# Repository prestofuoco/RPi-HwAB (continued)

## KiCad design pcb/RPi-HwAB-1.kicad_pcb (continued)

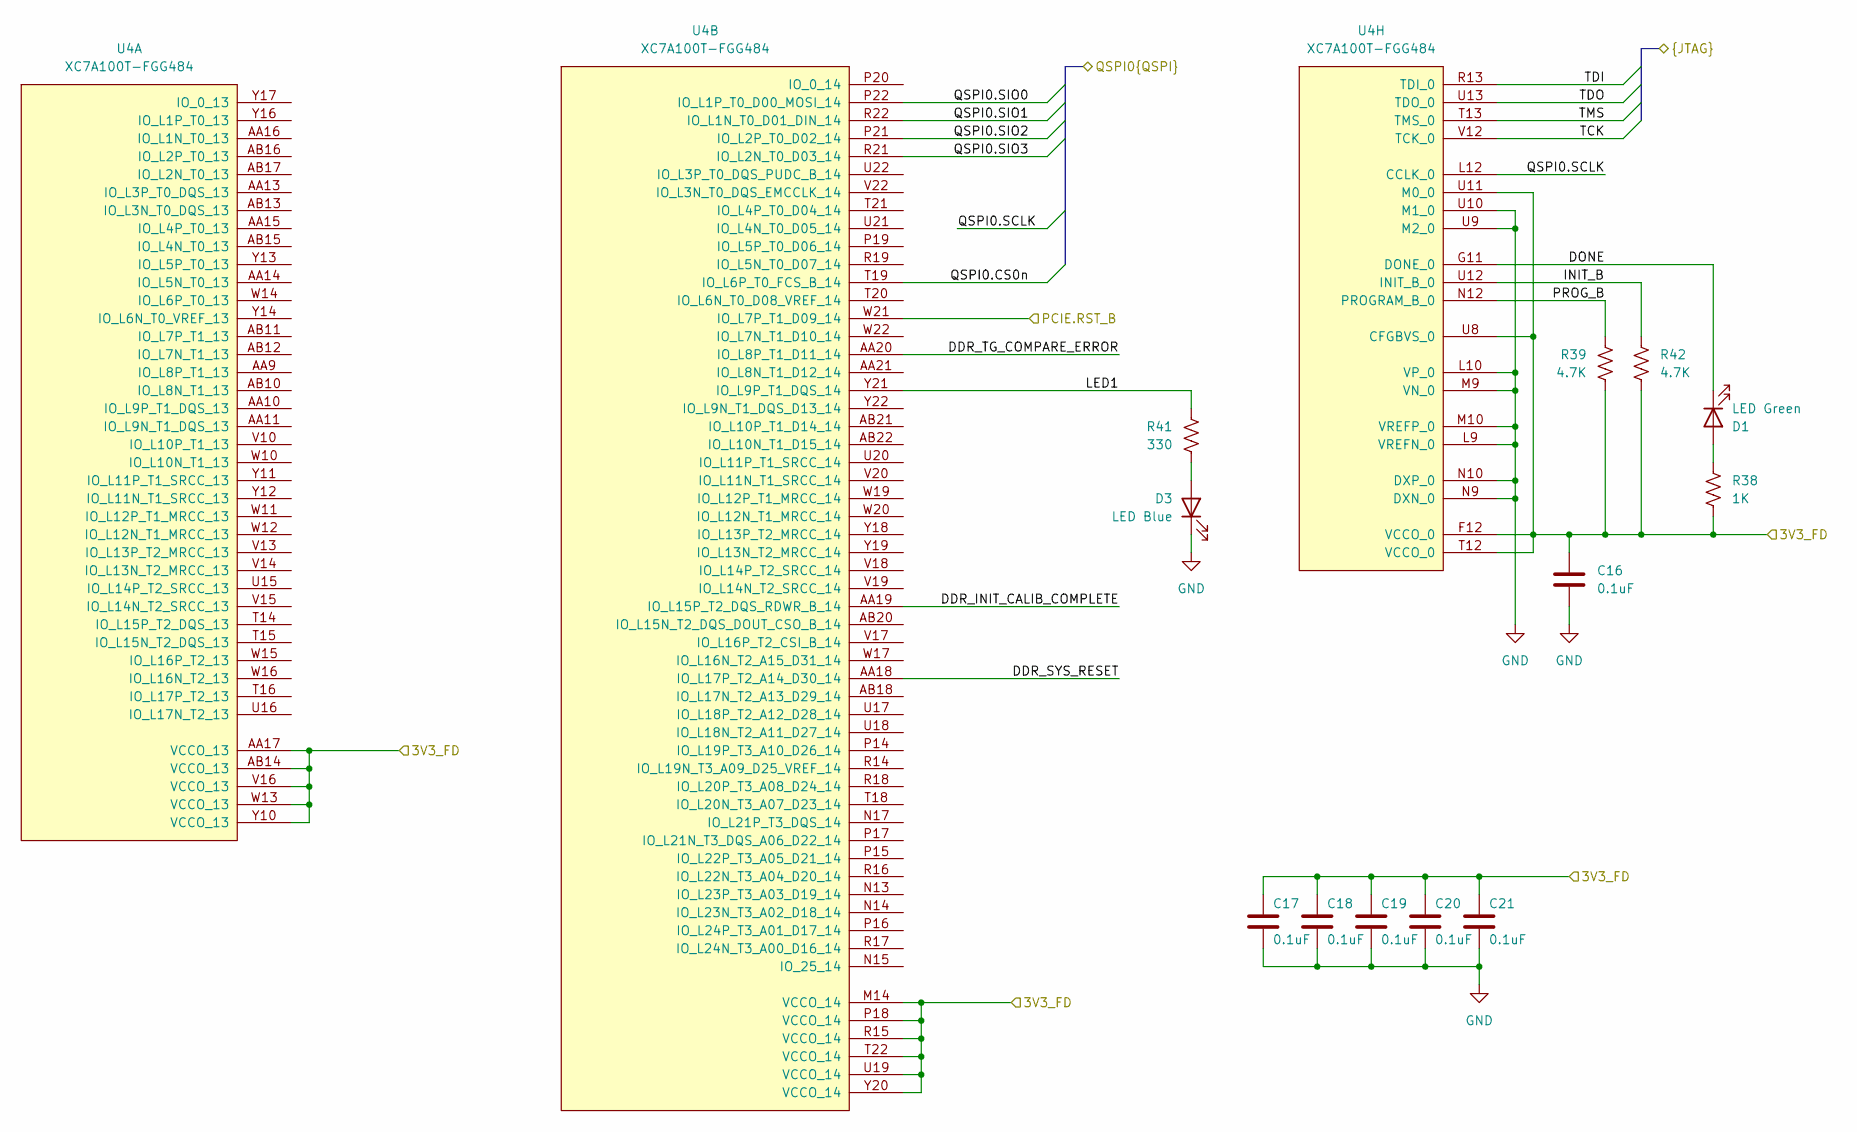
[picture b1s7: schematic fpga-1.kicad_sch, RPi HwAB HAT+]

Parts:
C16, C17, C18, C19, C20, C21: 0.1uF; C_0402_1005Metric; Part Description CAP CER 0.1UF 16V X7R 0402
D1: LED Green; LED_0603_1608Metric; Part Description LED GREEN CLEAR CHIP SMD
D3: LED Blue; LED_0603_1608Metric; Part Description LED BLUE CLEAR CHIP SMD
R38: 1K; R_0402_1005Metric; Part Description RES 1K OHM 5% 1/16W 0402
R39, R42: 4.7K; R_0402_1005Metric; Part Description RES 4.7K OHM 1% 1/16W 0402
R41: 330; R_0402_1005Metric; Part Description RES 330 OHM 1% 1/16W 0402
U4: XC7A100T-FGG484; Xilinx_FGG484; Part Description IC FPGA 285 I/O 484FBGA

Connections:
/Connectors/3V3_FD: C16.2, C17.2, C18.2, C19.2, C20.2, C21.2, R38.2, R39.2, R42.2, U4.AA17 (VCCO_13), U4.AB14 (VCCO_13), U4.F12 (VCCO_0), U4.M14 (VCCO_14), U4.P18 (VCCO_14), U4.R15 (VCCO_14), U4.T12 (VCCO_0), U4.T22 (VCCO_14), U4.U8 (CFGBVS_0), U4.U11 (M0_0), U4.U19 (VCCO_14), U4.V16 (VCCO_13), U4.W13 (VCCO_13), U4.Y10 (VCCO_13), U4.Y20 (VCCO_14); also elsewhere on the board
/Connectors/PCIE.RST_B: U4.W21 (IO_L7P_T1_D09_14); also elsewhere on the board
/Connectors/QSPI0.CS0n: U4.T19 (IO_L6P_T0_FCS_B_14); also elsewhere on the board
/Connectors/QSPI0.SCLK: U4.L12 (CCLK_0); also elsewhere on the board
/Connectors/QSPI0.SIO0: U4.P22 (IO_L1P_T0_D00_MOSI_14); also elsewhere on the board
/Connectors/QSPI0.SIO1: U4.R22 (IO_L1N_T0_D01_DIN_14); also elsewhere on the board
/Connectors/QSPI0.SIO2: U4.P21 (IO_L2P_T0_D02_14); also elsewhere on the board
/Connectors/QSPI0.SIO3: U4.R21 (IO_L2N_T0_D03_14); also elsewhere on the board
/Connectors/TCK: U4.V12 (TCK_0); also elsewhere on the board
/Connectors/TDI: U4.R13 (TDI_0); also elsewhere on the board
/Connectors/TDO: U4.U13 (TDO_0); also elsewhere on the board
/Connectors/TMS: U4.T13 (TMS_0); also elsewhere on the board
/FPGA/FPGA 0, 13, 14/DDR_INIT_CALIB_COMPLETE: U4.AA19 (IO_L15P_T2_DQS_RDWR_B_14)
/FPGA/FPGA 0, 13, 14/DDR_SYS_RESET: U4.AA18 (IO_L17P_T2_A14_D30_14)
/FPGA/FPGA 0, 13, 14/DDR_TG_COMPARE_ERROR: U4.AA20 (IO_L8P_T1_D11_14)
/FPGA/FPGA 0, 13, 14/DONE: D1.1 (K), U4.G11 (DONE_0)
/FPGA/FPGA 0, 13, 14/INIT_B: R42.1, U4.U12 (INIT_B_0)
/FPGA/FPGA 0, 13, 14/LED1: R41.1, U4.Y21 (IO_L9P_T1_DQS_14)
/FPGA/FPGA 0, 13, 14/PROG_B: R39.1, U4.N12 (PROGRAM_B_0)
unnamed: D1.2 (A), R38.1
unnamed: D3.2 (A), R41.2

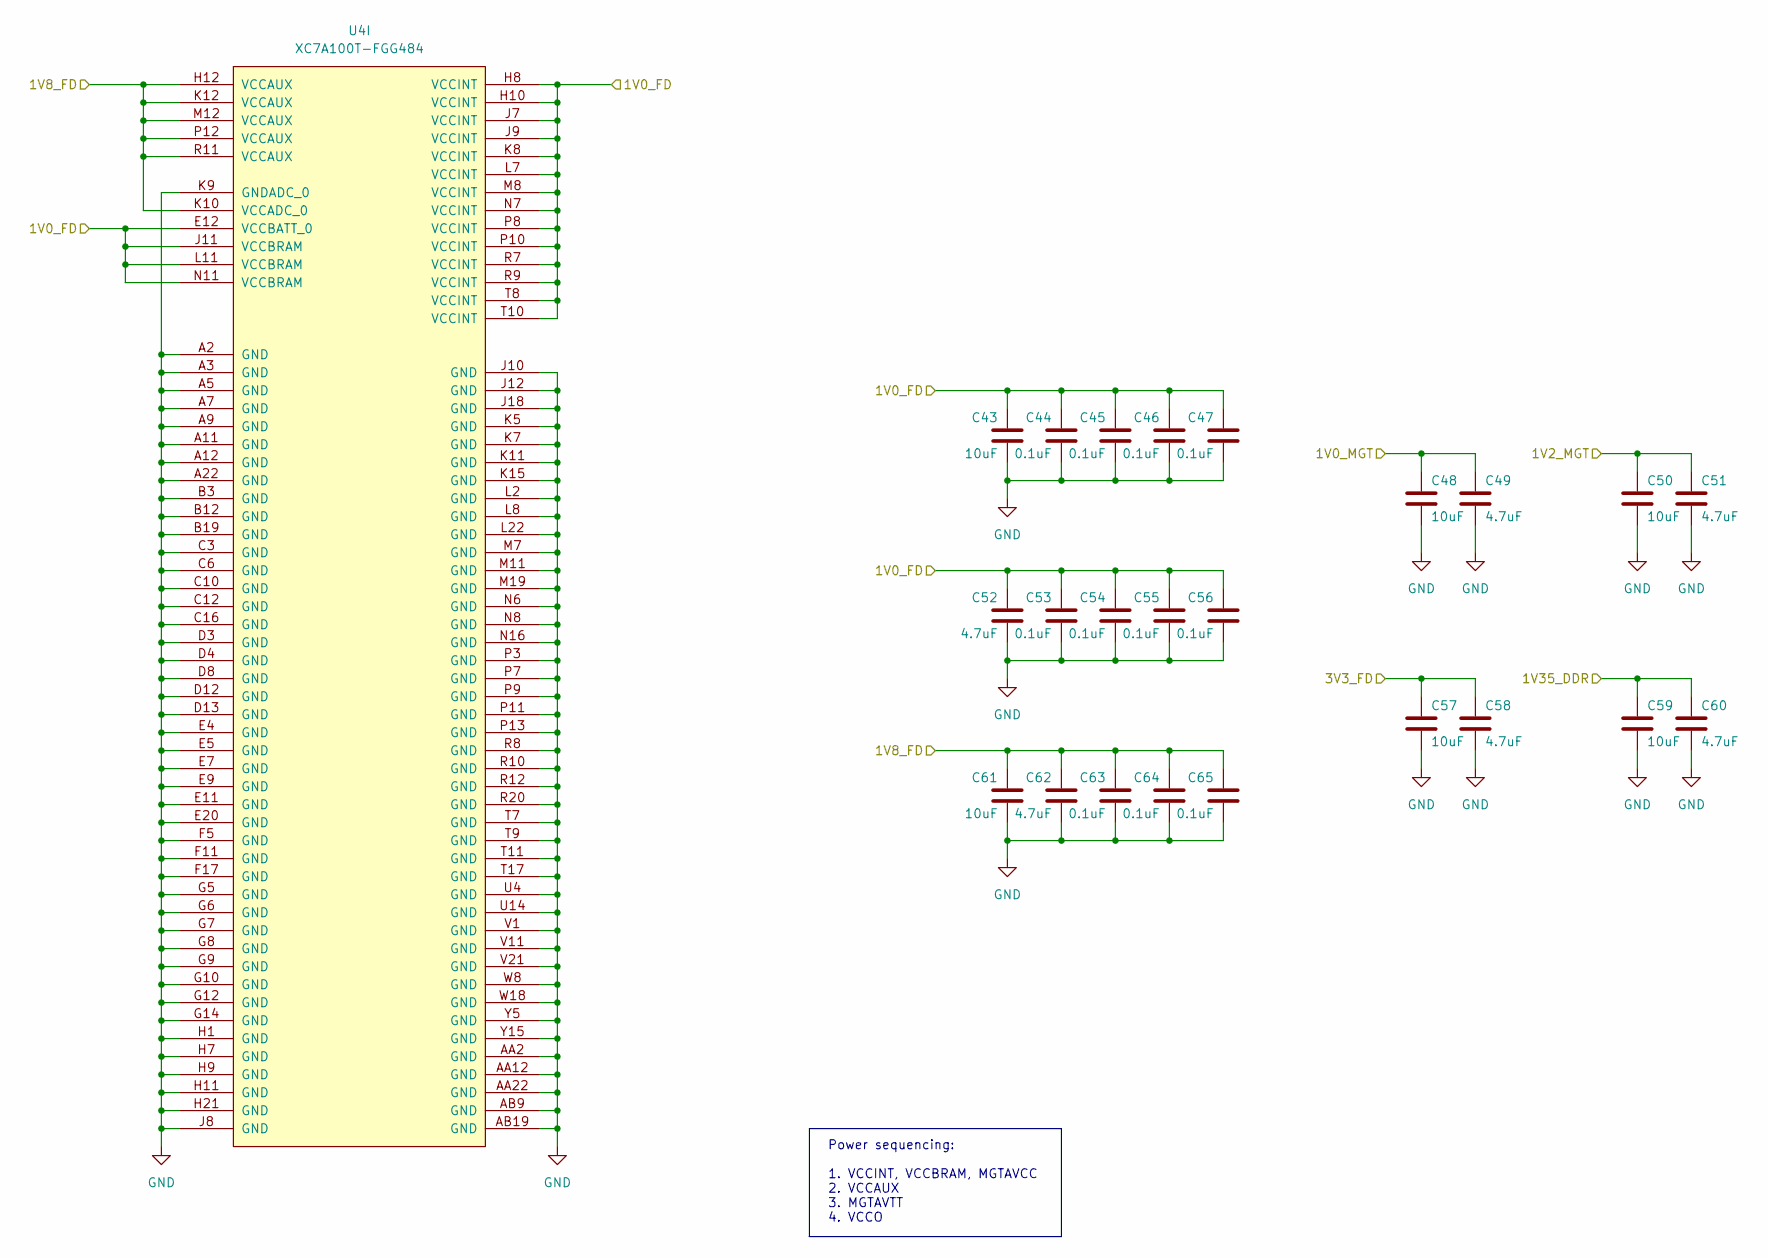
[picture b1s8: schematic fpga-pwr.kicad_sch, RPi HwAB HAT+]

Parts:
C43, C48, C50, C57, C59, C61: 10uF; C_1206_3216Metric; Part Description CAP TANT 10UF 20% 10V 1206
C44, C45, C46, C47, C53, C54, C55, C56, C63, C64, C65: 0.1uF; C_0402_1005Metric; Part Description CAP CER 0.1UF 16V X7R 0402
C49, C51, C52, C58, C60, C62: 4.7uF; C_0603_1608Metric; Part Description CAP CER 4.7UF 10V X5R 0603
U4: XC7A100T-FGG484; Xilinx_FGG484; Part Description IC FPGA 285 I/O 484FBGA

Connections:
/Connectors/3V3_FD: C57.1, C58.1; also elsewhere on the board
/Main Power/1V0_FD: C43.1, C44.2, C45.2, C46.2, C47.2, C52.1, C53.2, C54.2, C55.2, C56.2, U4.E12 (VCCBATT_0), U4.H8 (VCCINT), U4.H10 (VCCINT), U4.J7 (VCCINT), U4.J9 (VCCINT), U4.J11 (VCCBRAM), U4.K8 (VCCINT), U4.L7 (VCCINT), U4.L11 (VCCBRAM), U4.M8 (VCCINT), U4.N7 (VCCINT), U4.N11 (VCCBRAM), U4.P8 (VCCINT), U4.P10 (VCCINT), U4.R7 (VCCINT), U4.R9 (VCCINT), U4.T8 (VCCINT), U4.T10 (VCCINT); also elsewhere on the board
/Main Power/1V0_MGT: C48.1, C49.1; also elsewhere on the board
/Main Power/1V2_MGT: C50.1, C51.1; also elsewhere on the board
/Main Power/1V8_FD: C61.1, C62.1, C63.2, C64.2, C65.2, U4.H12 (VCCAUX), U4.K10 (VCCADC_0), U4.K12 (VCCAUX), U4.M12 (VCCAUX), U4.P12 (VCCAUX), U4.R11 (VCCAUX); also elsewhere on the board
/Main Power/1V35_DDR: C59.1, C60.1; also elsewhere on the board

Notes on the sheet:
Power sequencing: 1. VCCINT, VCCBRAM, MGTAVCC 2. VCCAUX 3. MGTAVTT 4. VCCO

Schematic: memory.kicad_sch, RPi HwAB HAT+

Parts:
C69, C71, C72, C73, C74: 0.1uF; C_0402_1005Metric; Part Description CAP CER 0.1UF 16V X7R 0402
C70: 4.7uF; C_0603_1608Metric; Part Description CAP CER 4.7UF 10V X5R 0603
R20: 240 1%; R_0402_1005Metric; Part Description RES 240 OHM 1% 1/16W 0402
R31, R32: 2.2K 1%; R_0402_1005Metric; Part Description RES 2.2K OHM 1% 1/16W 0402
U6: MT41K256M16TW-107:P TR; Micron_FBGA-96_7.5x13.5mm_Layout9x16_P0.8mm; Part Description IC DRAM 4GBIT PAR 96FBGA
U7: MX25L12835F; WSON-8-1EP_6x5mm_P1.27mm_EP3.4x4mm; Part Description IC FLASH 128MBIT SPI 8WSON

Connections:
/Connectors/3V3_FD: C74.2, U7.8 (VCC); also elsewhere on the board
/Connectors/QSPI0.CS0n: U7.1 (~CS); also elsewhere on the board
/Connectors/QSPI0.SCLK: U7.6 (SCLK); also elsewhere on the board
/Connectors/QSPI0.SIO0: U7.5 (SI/SIO0); also elsewhere on the board
/Connectors/QSPI0.SIO1: U7.2 (SO/SIO1); also elsewhere on the board
/Connectors/QSPI0.SIO2: U7.3 (~WP/SIO2); also elsewhere on the board
/Connectors/QSPI0.SIO3: U7.7 (~HOLD/SIO3); also elsewhere on the board
/FPGA/FPGA 34, 35/A0: U6.N3 (A0); also elsewhere on the board
/FPGA/FPGA 34, 35/A1: U6.P7 (A1); also elsewhere on the board
/FPGA/FPGA 34, 35/A2: U6.P3 (A2); also elsewhere on the board
/FPGA/FPGA 34, 35/A3: U6.N2 (A3); also elsewhere on the board
/FPGA/FPGA 34, 35/A4: U6.P8 (A4); also elsewhere on the board
/FPGA/FPGA 34, 35/A5: U6.P2 (A5); also elsewhere on the board
/FPGA/FPGA 34, 35/A6: U6.R8 (A6); also elsewhere on the board
/FPGA/FPGA 34, 35/A7: U6.R2 (A7); also elsewhere on the board
/FPGA/FPGA 34, 35/A8: U6.T8 (A8); also elsewhere on the board
/FPGA/FPGA 34, 35/A9: U6.R3 (A9); also elsewhere on the board
/FPGA/FPGA 34, 35/A10: U6.L7 (A10/AP); also elsewhere on the board
/FPGA/FPGA 34, 35/A11: U6.R7 (A11); also elsewhere on the board
/FPGA/FPGA 34, 35/A12: U6.N7 (A12/~BC); also elsewhere on the board
/FPGA/FPGA 34, 35/A13: U6.T3 (A13); also elsewhere on the board
/FPGA/FPGA 34, 35/A14: U6.T7 (A14); also elsewhere on the board
/FPGA/FPGA 34, 35/DDR_BA0: U6.M2 (BA0); also elsewhere on the board
/FPGA/FPGA 34, 35/DDR_BA1: U6.N8 (BA1); also elsewhere on the board
/FPGA/FPGA 34, 35/DDR_BA2: U6.M3 (BA2); also elsewhere on the board
/FPGA/FPGA 34, 35/DDR_CASn: U6.K3 (~CAS); also elsewhere on the board
/FPGA/FPGA 34, 35/DDR_CKE: U6.K9 (CKE); also elsewhere on the board
/FPGA/FPGA 34, 35/DDR_CK_N: U6.K7 (~CK); also elsewhere on the board
/FPGA/FPGA 34, 35/DDR_CK_P: U6.J7 (CK); also elsewhere on the board
/FPGA/FPGA 34, 35/DDR_CSn: U6.L2 (~CS); also elsewhere on the board
/FPGA/FPGA 34, 35/DDR_LDM: U6.E7 (LDM); also elsewhere on the board
/FPGA/FPGA 34, 35/DDR_LDQS_N: U6.G3 (~LDQS); also elsewhere on the board
/FPGA/FPGA 34, 35/DDR_LDQS_P: U6.F3 (LDQS); also elsewhere on the board
/FPGA/FPGA 34, 35/DDR_ODT: U6.K1 (ODT); also elsewhere on the board
/FPGA/FPGA 34, 35/DDR_RASn: U6.J3 (~RAS); also elsewhere on the board
/FPGA/FPGA 34, 35/DDR_RESETn: U6.T2 (~RESET); also elsewhere on the board
/FPGA/FPGA 34, 35/DDR_UDM: U6.D3 (UDM); also elsewhere on the board
/FPGA/FPGA 34, 35/DDR_UDQS_N: U6.B7 (~UDQS); also elsewhere on the board
/FPGA/FPGA 34, 35/DDR_UDQS_P: U6.C7 (UDQS); also elsewhere on the board
/FPGA/FPGA 34, 35/DDR_WEn: U6.L3 (~WE); also elsewhere on the board
/FPGA/FPGA 34, 35/DQ0: U6.E3 (DQ0); also elsewhere on the board
/FPGA/FPGA 34, 35/DQ1: U6.F7 (DQ1); also elsewhere on the board
/FPGA/FPGA 34, 35/DQ2: U6.F2 (DQ2); also elsewhere on the board
/FPGA/FPGA 34, 35/DQ3: U6.F8 (DQ3); also elsewhere on the board
/FPGA/FPGA 34, 35/DQ4: U6.H3 (DQ4); also elsewhere on the board
/FPGA/FPGA 34, 35/DQ5: U6.H8 (DQ5); also elsewhere on the board
/FPGA/FPGA 34, 35/DQ6: U6.G2 (DQ6); also elsewhere on the board
/FPGA/FPGA 34, 35/DQ7: U6.H7 (DQ7); also elsewhere on the board
/FPGA/FPGA 34, 35/DQ8: U6.D7 (DQ8); also elsewhere on the board
/FPGA/FPGA 34, 35/DQ9: U6.C3 (DQ9); also elsewhere on the board
/FPGA/FPGA 34, 35/DQ10: U6.C8 (DQ10); also elsewhere on the board
/FPGA/FPGA 34, 35/DQ11: U6.C2 (DQ11); also elsewhere on the board
/FPGA/FPGA 34, 35/DQ12: U6.A7 (DQ12); also elsewhere on the board
/FPGA/FPGA 34, 35/DQ13: U6.A2 (DQ13); also elsewhere on the board
/FPGA/FPGA 34, 35/DQ14: U6.B8 (DQ14); also elsewhere on the board
/FPGA/FPGA 34, 35/DQ15: U6.A3 (DQ15); also elsewhere on the board
/Main Power/1V35_DDR: C71.2, C72.2, C73.2, R20.2, R31.1, U6.A1 (V_{DDQ}), U6.A8 (V_{DDQ}), U6.B2 (V_{DD}), U6.C1 (V_{DDQ}), U6.C9 (V_{DDQ}), U6.D2 (V_{DDQ}), U6.D9 (V_{DD}), U6.E9 (V_{DDQ}), U6.F1 (V_{DDQ}), U6.G7 (V_{DD}), U6.H2 (V_{DDQ}), U6.H9 (V_{DDQ}), U6.K2 (V_{DD}), U6.K8 (V_{DD}), U6.N1 (V_{DD}), U6.N9 (V_{DD}), U6.R1 (V_{DD}), U6.R9 (V_{DD}); also elsewhere on the board
unnamed: C69.2, C70.1, R31.2, R32.1, U6.H1 (V_{REFDQ}), U6.M8 (V_{REFCA})
unnamed: R20.1, U6.L8 (ZQ)

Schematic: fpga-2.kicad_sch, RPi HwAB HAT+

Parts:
C22, C23, C24, C25, C26, C27: 0.1uF; C_0402_1005Metric; Part Description CAP CER 0.1UF 16V X7R 0402
U4: XC7A100T-FGG484; Xilinx_FGG484; Part Description IC FPGA 285 I/O 484FBGA

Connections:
/Connectors/3V3_FD: C22.2, C23.2, C24.2, C25.2, C26.2, C27.2, U4.A17 (VCCO_16), U4.B14 (VCCO_16), U4.C21 (VCCO_16), U4.D18 (VCCO_16), U4.E15 (VCCO_16), U4.F22 (VCCO_16), U4.G19 (VCCO_15), U4.H16 (VCCO_15), U4.J13 (VCCO_15), U4.K20 (VCCO_15), U4.L17 (VCCO_15), U4.N21 (VCCO_15); also elsewhere on the board

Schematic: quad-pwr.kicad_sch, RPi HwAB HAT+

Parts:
C7, C8, C9, C10, C11: 2.2uF; C_0603_1608Metric; Part Description CAP CER 2.2UF 25V X5R 0603
C12, C13, C14, C15: 22uF; C_0603_1608Metric; Part Description CAP CER 22UF 10V X5R 0603
L1, L2, L3, L4: 1.5uH; L_Coilcraft_XAL4020-XXX; Part Description FIXED IND 1.5UH 7.5A 23.6MOHM SM
R12, R13, R14, R15: 22K; R_0402_1005Metric; Part Description RES 22K OHM 1% 1/16W 0402
U3: MAX20029; WQFN-28-1EP_4x4mm_P0.4mm_EP2.7x2.7mm; Part Description IC REG BUCK ADJ 1.5A QUAD 28TQFN

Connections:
/Connectors/3V3_FD: C13.1, L3.2, U3.14 (OUTS3); also elsewhere on the board
/Main Power/1V0/1V0_PG: U3.1 (EN1); also elsewhere on the board
/Main Power/1V2_MGT: C12.1, L4.2, U3.22 (OUTS4); also elsewhere on the board
/Main Power/1V8_FD: C15.1, L1.2, U3.28 (OUTS1); also elsewhere on the board
/Main Power/1V35_DDR: C14.1, L2.2, U3.8 (OUTS2); also elsewhere on the board
/Main Power/3V3_PG: R13.1, U3.12 (PG3); also elsewhere on the board
/Main Power/5V0_N: C7.1, C8.1, C9.1, C10.1, C11.1, R12.2, R13.2, R14.2, R15.2, U3.2 (PV1), U3.7 (PV2), U3.15 (PV3), U3.20 (PV4), U3.26 (VA); also elsewhere on the board
/Main Power/Quad Buck/1V2_PG: R12.1, U3.9 (EN2), U3.13 (EN3), U3.23 (PG4)
/Main Power/Quad Buck/1V8_PG: R15.1, U3.21 (EN4), U3.27 (PG1)
/Main Power/Quad Buck/1V35_PG: R14.1, U3.10 (PG2)
/Main Power/Quad Buck/LX1: L1.1, U3.3 (LX1)
/Main Power/Quad Buck/LX2: L2.1, U3.6 (LX2)
/Main Power/Quad Buck/LX3: L3.1, U3.16 (LX3)
/Main Power/Quad Buck/LX4: L4.1, U3.19 (LX4)

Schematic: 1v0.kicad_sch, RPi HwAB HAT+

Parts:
C3: 22uF; C_0603_1608Metric; Part Description CAP CER 22UF 10V X5R 0603
C4: 0.1uF; C_0402_1005Metric; Part Description CAP CER 0.1UF 16V X7R 0402
C5: 10uF; C_1206_3216Metric; Part Description CAP TANT 10UF 20% 10V 1206
C6: 4.7nF; C_0402_1005Metric; Part Description CAP CER 0402 4.7NF 50V X7R 5%
FB1: 120R @ 100MHz; L_0603_1608Metric; Part Description FERRITE BEAD 120 OHM 0603 1LN
R6: 0.005; R_1206_3216Metric; Part Description RES 0.005 OHM 1% 1W 1206
R7: 10K 1%; R_0402_1005Metric; Part Description RES 10K OHM 1% 1/16W 0402
R8, R9: 10; R_0402_1005Metric; Part Description RES 10 OHM 1% 1/16W 0402
R10: 15K 1%; R_0402_1005Metric; Part Description RES 15K OHM 1% 1/16W 0402
R11: 22K; R_0402_1005Metric; Part Description RES 22K OHM 1% 1/16W 0402
U2: TPSM82903; TPSM82903SISR; Part Description 3-V TO 17-V, 3-A, HIGH-EFFICIENC

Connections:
/Connectors/PCIE.PWR_EN: U2.3 (EN); also elsewhere on the board
/Main Power/1V0/1V0_FB: R7.2, R10.1, U2.7 (FB/VSET)
/Main Power/1V0/1V0_P: C3.1, R6.2, R7.1, R8.2, U2.9 (VOUT), U2.10 (VOUT)
/Main Power/1V0/1V0_PG: R11.1, U2.6 (PG); also elsewhere on the board
/Main Power/1V0_FD: FB1.1, R6.1, R9.2; also elsewhere on the board
/Main Power/1V0_MGT: FB1.2; also elsewhere on the board
/Main Power/1V0_SENS_N: C4.1, R8.1; also elsewhere on the board
/Main Power/1V0_SENS_P: C4.2, R9.1; also elsewhere on the board
/Main Power/5V0_N: C5.1, R11.2, U2.1 (VIN), U2.2 (VIN), U2.4 (MODE); also elsewhere on the board
unnamed: C6.1, U2.5 (SS/TR)

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
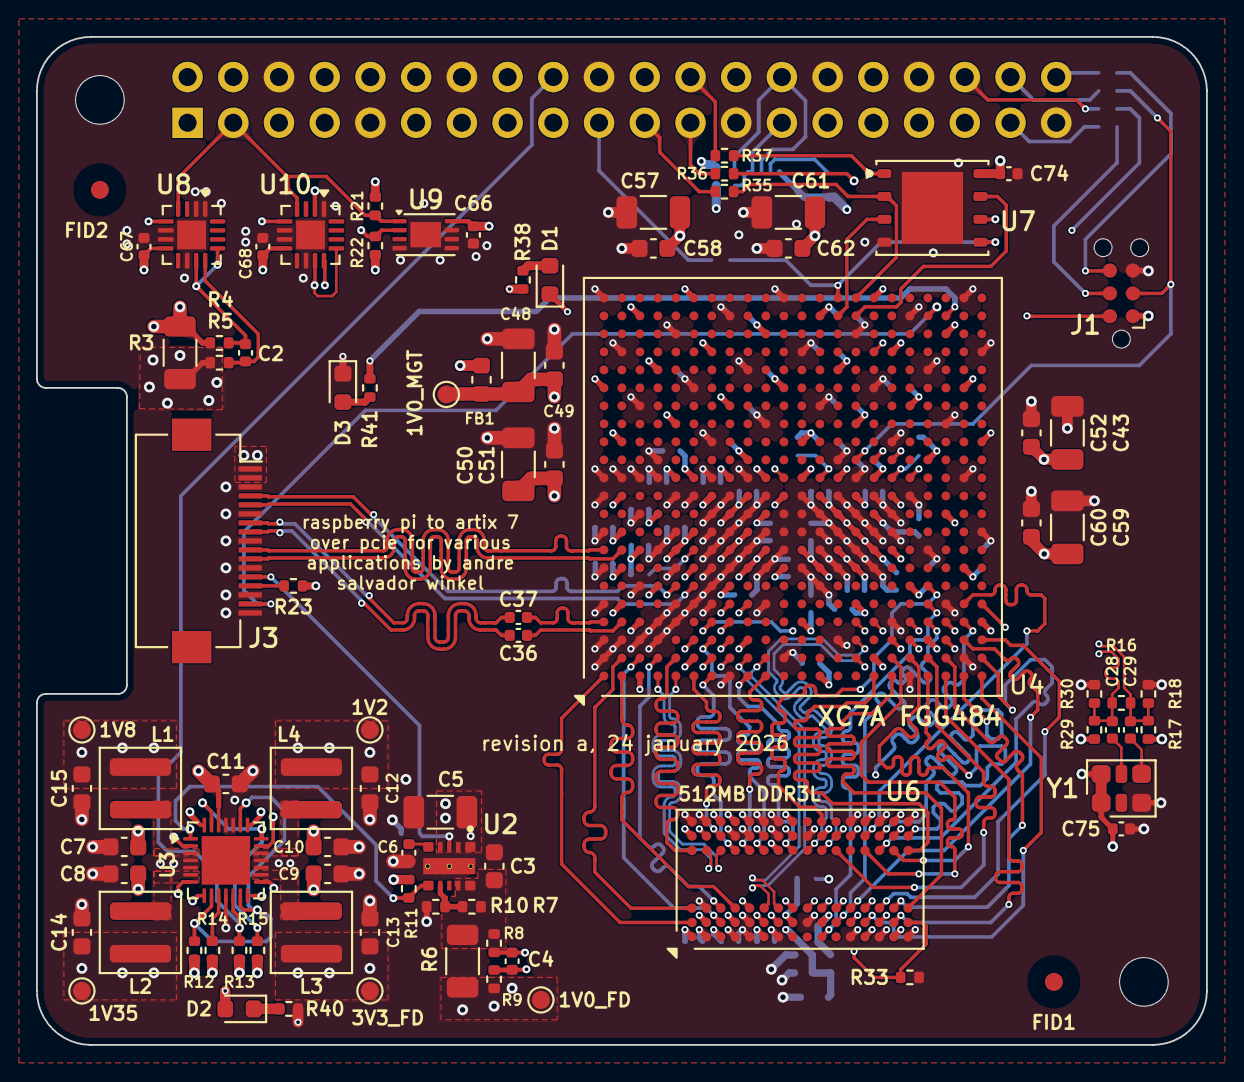
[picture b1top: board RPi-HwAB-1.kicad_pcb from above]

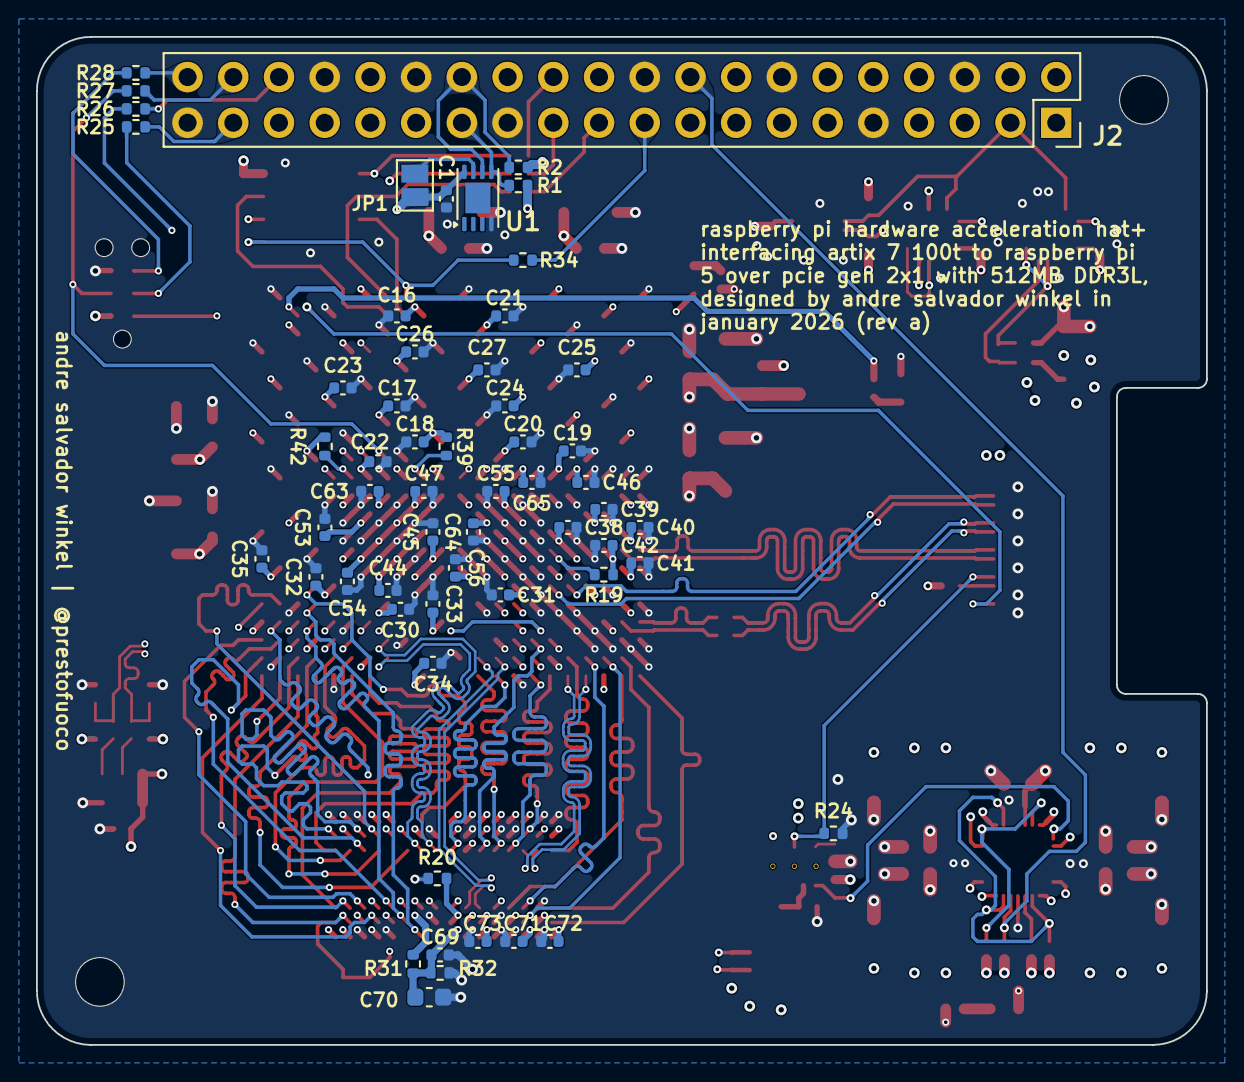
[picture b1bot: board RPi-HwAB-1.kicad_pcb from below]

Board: 8 copper layers, 65.0 x 56.0 mm, 149 parts (57 on the bottom side), 123 nets.

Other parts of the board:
1V0_FD, 1V0_MGT, 1V2, 1V8, 1V35, 3V3_FD: TestPoint; TestPoint_Pad_D1.0mm
MH1, MH4: MountingHole_2.7mm_M2.5

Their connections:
/Connectors/3V3_FD: 3V3_FD.1 (1_1); also elsewhere on the board
/Main Power/1V0_FD: 1V0_FD.1 (1_1); also elsewhere on the board
/Main Power/1V0_MGT: 1V0_MGT.1 (1_1); also elsewhere on the board
/Main Power/1V2_MGT: 1V2.1 (1_1); also elsewhere on the board
/Main Power/1V8_FD: 1V8.1 (1_1); also elsewhere on the board
/Main Power/1V35_DDR: 1V35.1 (1_1); also elsewhere on the board

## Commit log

2025-08-23 file restructuring
    redefined naming scheme for schematic files (fpga-num) etc.
2025-08-23 Add initial README for rpihwab project
2025-08-23 Add MIT License to the project
2025-08-23 Update license file reference in README
2025-08-23 restructure project
2025-08-23 changed email spacing
2025-08-23 Correct 'kicad/altium' to 'kicad' in README
2025-08-23 current sense, fpga power sequencing
    plus restructuring files
2025-08-23 add sensors, hierarchical changes
2025-08-23 addl. updates to power hierarchy
2025-08-24 added power sequencing through raspi gpio
    additionally defined sensors
2025-08-24 Fix typo and update wording in README.md
    Corrected a typo in the hardware section and adjusted wording in the PCB design section.
2025-08-24 quick edits to hierarchy
2025-08-24 added power supply simulations
2025-08-24 Add simulations directory to README structure
2025-08-24 Add initial README for PCB project
2025-08-24 Replace schematic image with updated version
    Updated the schematic image in the README.
2025-08-25 defined pcie diff. connections
2025-08-25 removed redundant sheet
2025-08-25 updated sims
    unfinished
2025-08-25 housekeeping
2025-08-25 connected jtag-fpga, tc2030
2025-08-25 Update schematic date and image in README
2025-08-25 created vivado project
2025-08-25 created vivado test project
2025-08-25 Update fpga_src status and add subdirectories
2025-08-25 broke the whole thing
2025-08-29 reorg hierarchical, define buses
    added bus definitions, aliasing, reorganized sub-sheets for hierarchical interpretation, grouped fpga. pending dram and mram addition
2025-08-29 fixed page numbering
    per previous commit
2025-08-29 Fix project link in README.md
2025-08-30 completed bus aliasing definitions
2025-08-30 Update top-level schematic date and image link
2025-08-30 Remove empty line in hardware requirements
    Removed an empty line in the hardware requirements section.
2025-08-30 Update README with hardware requirements
2025-08-30 updated sims, power hierarchy
    added power flags to voltage buses, removed standard kicad "+3.3V" power flags and using standard kicad "power flag" in order to use hierarchical labels to visually show power paths
2025-08-30 updated power hierarchy and sims
2025-08-30 more power sims
2025-08-31 added main ip blocks
2025-09-01 adp5054 1.2v and 1.0v rough
    rough draft of power sims, looking good so far!
2025-09-01 more pwr sims
2025-09-02 Add .raw files to .gitignore
2025-09-03 edits to simulations
2025-09-03 power supply template~?
2025-09-03 ibis for hyperlynx
2025-09-03 adp5054 spice sims update
2025-09-03 Update README with power requirements and details
2025-09-03 Update README with power supply requirements
2025-09-03 added 1.8v to sim
2025-09-04 more sims
2025-09-05 more sims of one channel
    because doing them all at once is so slow
2025-09-05 power pins
2025-09-07 1v0 and 1v8 decoupling sims
2025-09-15 decoupling
2025-09-15 removed zip from git
2025-09-16 buck outputs
2025-09-17 restructured power hierarchy
2025-09-17 power supply comp abstraction
2025-09-17 cleaning
2025-09-17 hierarchical current sense
2025-09-17 Fix formatting of schematic hierarchy in README
2025-09-17 readme hierarchy description spacing
    Updated schematic hierarchy structure in README.
2025-09-17 cleanup
2025-09-19 current sense hierarchy definition
2025-09-19 power flags
2025-09-19 changed spi flash to wson
2025-09-21 removed one I-sense
2025-09-21 fpga decoupling
2025-09-21 pcie definitions
2025-09-26 decoupling for 3v3_fd
2025-09-26 added dram, defined pcie sideband sigs.
2025-10-01 ddr3
2025-10-11 Refactor README for clarity and organization
    Updated README.md to improve clarity and structure.
2025-10-11 Fix project link formatting in README.md
2025-10-15 added potential power sequencer
2025-11-03 saved libraries to project
2025-11-03 sequencing initial connections
2025-11-04 hierarchy and power sequencing, level shift
2025-11-04 added hierarchical sheet, pwr seq
2025-11-04 Update README with new schematic date and remove details
    Removed outdated power requirements and development status.
2025-12-19 defined memory pinouts
2026-01-02 power restructuring
2026-01-03 changes to power tree
2026-01-03 moved stuff around, bom
2026-01-04 jtag, dcplng
2026-01-04 qspi
2026-01-05 power cleanup, pdf sch
2026-01-05 quick fix top-level sch
2026-01-05 updated top-level schematic image
2026-01-06 initial layout, dogbone fanout
2026-01-07 added mig ddr pinout constraints
2026-01-08 real ddr pinout done
2026-01-10 restructured power, power plane layout
2026-01-10 updated sch plot
2026-01-12 dogbone for ddr
2026-01-13 vref
2026-01-14 change to 8 layers, impedance calc, ddr routing
2026-01-14 ddr addr routing
2026-01-15 length matched ddr upper and lower data bytes, pending address
2026-01-15 power plane apportionment redid power planes, clearance to 0.2mm, most on l5, some on l6
2026-01-24 ported to nightly, finished ddr routing yay!!!!!!! pcb/v1.0 almost complete!
2026-01-24 routing done! pcb/v1.0 almost ready for release added series resistors from raspi spi to qspi, all nets connected and routed
2026-01-24 quick fix pcie length matching w/ better nightly build previous rev kicad (current rel?) was being bad for length matching through layers, or something like that. just adjusted skew for pcie 2x1 trac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
2026-01-24 complete! added and prettied up silkscreen
2026-01-24 added workflow
2026-01-24 deleted workflow
2026-01-24 add kibot workflow
2026-01-24 switch CI to kicad nightly
2026-01-24 force kibot to use nightly docker img
2026-01-24 try again
2026-01-24 try to fix
2026-01-24 use kicad nightly
2026-01-24 try to find cli
2026-01-24 new image
2026-01-24 root
2026-01-24 add kicad library to step export
2026-01-24 fix files for ubuntu
2026-01-24 add more flags
2026-01-24 change to glb
2026-01-24 fixed glb
2026-01-24 changed drill origin
2026-01-24 added slksc and sldrmsk
2026-01-24 added schematic and layer views to ci/cd export
2026-01-24 cleaned pcb export ci/cd
2026-01-24 removed redundancy [skip ci]
2026-01-27 added jlc fab
2026-01-27 remove readme, add jlc [skip ci]
